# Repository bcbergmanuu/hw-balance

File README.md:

# Hardware deisgn balanceboard

Design Goals
  - Four measureable legs
  - USB 3 powered (<950mA)
  - Ultralow RMS Noise ldo (0.8µVRMS)
  - 10v Excitation voltage
  - Precision crystal clock fir filtering (20ppm)
  - Class c3 Loadcells type [LA250-D-100kg](https://allscaleseurope.com/content/uploads/2018/01/LA250-D-single-point-load-cell.pdf)
  - 8 bit decoupled auxiliary pc input
  - 24 bit ADC (ad7124)  

Balanceboard design

LTspice simulation LDO | Boost converters

Schematic Kicad | 3d-view of bcp

Errata:
R19 48K, should be 390
R3 should be removed

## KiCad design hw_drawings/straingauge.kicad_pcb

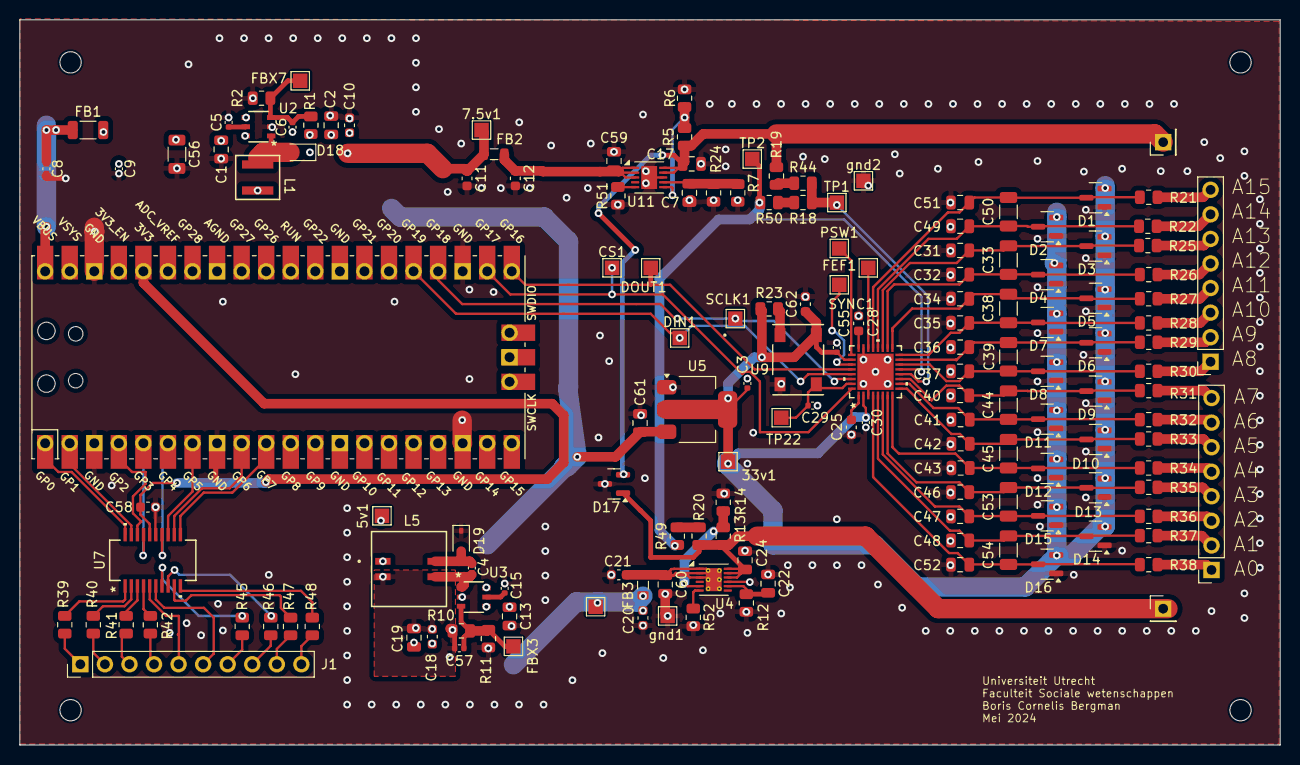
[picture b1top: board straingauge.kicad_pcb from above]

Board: 4 copper layers, 130.3 x 75.0 mm, 161 parts (0 on the bottom side), 98 nets.

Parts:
5v1, 7.5v1, 33v1: TestPoint_Pad_1.5x1.5mm
-3.8v1: TestPoint_Pad_1.5x1.5mm
C1, C2, C13, C17, C19, C24, C59, C60, C61: 10u; C_0805_2012Metric
C3, C4, C5, C8, C9, C15, C30, C55: 1u; C_0402_1005Metric
C6, C57: 4.7p; C_0402_1005Metric
C7, C22: 4.7u; C_0805_2012Metric
C10, C18, C25, C28, C58, C62: .1u; C_0603_1608Metric
C11, C12, C20, C21: 2.2u; C_0603_1608Metric
C29: 15p; C_0402_1005Metric
C31, C32, C34, C35, C36, C37, C40, C41, C42, C43, C46, C47, C48, C49, C51, C52: 10n; C_0805_2012Metric
C33, C38, C39, C44, C45, C50, C53, C54: 100n; C_1206_3216Metric
C56: 47u; R_1206_3216Metric
CS1: TestPoint_Pad_1.5x1.5mm
D1, D2, D3, D4, D5, D6, D7, D8, D9, D10, D11, D12, D13, D14, D15, D16: BAT54S; SOT-23
D17: BAV99; SOT-23
D18, D19: 1N5819WS; D_SOD-323
DIN1: TestPoint_Pad_1.5x1.5mm
DOUT1: TestPoint_Pad_1.5x1.5mm
FB1: 500 2A; L_1206_3216Metric
FB2, FB3: 120 1A; L_0805_2012Metric
FBX3, FBX7: TestPoint_Pad_1.5x1.5mm
FEF1: TestPoint_Pad_1.5x1.5mm
H1, H2, H3, H4: MountingHole_Pad; MountingHole_2.2mm_M2
J1: Conn_01x10_Pin; PinHeader_1x10_P2.54mm_Vertical
J2, J3: Conn_01x08_Pin; PinSocket_1x08_P2.54mm_Vertical
J4, J5: Pin; PinHeader_1x01_P2.54mm_Vertical
L1: XGL4020-152MEC; IND_XGL4020_COC
L5: 2.5u; IC4_MSD7342-252MLB_COC
PSW1: TestPoint_Pad_1.5x1.5mm
R1, R5, R10, R13: 1M; R_0805_2012Metric
R2, R11: 270K; R_0805_2012Metric
R6: 47K; R_0805_2012Metric
R7: 68k; R_0805_2012Metric
R12: 30k; R_0805_2012Metric
R14: 120K; R_0805_2012Metric
R18: 240; R_0805_2012Metric
R19: 430; R_0805_2012Metric
R20, R44, R50: 10; R_0805_2012Metric
R21, R22, R25, R26, R27, R28, R29, R30, R31, R32, R33, R34, R35, R36, R37, R38: 100; R_0805_2012Metric
R23: 1k; R_0805_2012Metric
R24: 2K; R_0805_2012Metric
R39, R40, R41, R42, R45, R46, R47, R48, R51: 680; R_0805_2012Metric
R49: 300; R_0805_2012Metric
R52: 16k; R_0805_2012Metric
SCLK1: TestPoint_Pad_1.5x1.5mm
SYNC1: TestPoint_Pad_1.5x1.5mm
TP1, TP2, TP22: TestPoint_Pad_1.5x1.5mm
U1: AD7124-8BCPZ; CP_32_12_ADI
U2, U3: LT8330ES6; TSOT-23_S6_LIT
U4: LT3094xDD; DFN-12-1EP_3x3mm_P0.45mm_EP1.65x2.38mm_ThermalVias
U5: AMS1117-3.3; SOT-223-3_TabPin2
U6: Pico; RPi_Pico_SMD_TH
U7: SI8380PM-IU; QSOP20_SIL
U9: SIT8008BC-83-33E-2.4576; SIT8008BC-83-33E-10.000000_SIT
U11: LT3045xDD; DFN-10-1EP_3x3mm_P0.5mm_EP1.65x2.38mm
gnd1, gnd2: TestPoint_Pad_1.5x1.5mm

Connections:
+3.3V: 33v1.1, C3.1, C30.1, C55.1, C62.1, D1.2 (K), D2.2 (K), D3.2 (K), D4.2 (K), D5.2 (K), D6.2 (K), D7.2 (K), D8.2 (K), D9.2 (K), D10.2 (K), D11.2 (K), D12.2 (K), D13.2 (K), D14.2 (K), D15.2 (K), D16.2 (K), R23.1, U1.2 (IOVDD), U1.26 (AVDD), U5.2 (VO), U9.4 (VDD)
+3.3VP: C58.1, U6.36 (3V3), U7.16 (VDD)
+5V: 5v1.1, C1.1, C9.1, C13.1, C56.1, C61.1, FB1.2, L1.2, L5.1, U2.4 (EN/UVLO), U2.6 (VIN), U3.4 (EN/UVLO), U3.6 (VIN), U5.3 (VI)
+5VP: C8.1, FB1.1, U6.40 (VBUS)
+7V: C17.1, D17.2 (A), J4.1, R5.1, R19.1, U11.9 (OUTS), U11.10 (OUT)
-3v: C24.1, D17.1 (K), J5.1, R13.2, R20.2, U4.10 (OUTS), U4.11 (OUT), U4.12 (OUT)
/7.526v: 7.5v1.1, C2.1, C6.1, C10.1, C11.1, D18.1 (K), FB2.1, R1.1
/*CS: CS1.1, U1.32 (*CS), U6.22 (GPIO17)
/-3.76v: -3.8v1.1, C18.2, C19.1, C20.1, C57.1, FB3.1, L5.2, R10.2
/AIN0: C52.2, C54.1, D16.3 (COM), R38.1, U1.4 (AIN0/IOUT/VBIAS)
/AIN0_C: J3.1, R38.2
/AIN1: C48.1, C54.2, D14.3 (COM), R37.1, U1.5 (AIN1/IOUT/VBIAS)
/AIN1_C: J3.2, R37.2
/AIN2: C47.2, C53.1, D15.3 (COM), R36.1, U1.6 (AIN2/IOUT/VBIAS/P1)
/AIN2_C: J3.3, R36.2
/AIN3: C46.1, C53.2, D13.3 (COM), R35.1, U1.7 (AIN3/IOUT/VBIAS/P2)
/AIN3_C: J3.4, R35.2
/AIN4: C43.2, C45.1, D12.3 (COM), R34.1, U1.8 (AIN4/IOUT/VBIAS/P3)
/AIN4_C: J3.5, R34.2
/AIN5: C42.1, C45.2, D10.3 (COM), R33.1, U1.9 (AIN5/IOUT/VBIAS/P4)
/AIN5_C: J3.6, R33.2
/AIN6: C41.2, C44.1, D11.3 (COM), R32.1, U1.10 (AIN6/IOUT/VBIAS)
/AIN6_C: J3.7, R32.2
/AIN7: C40.1, C44.2, D9.3 (COM), R31.1, U1.11 (AIN7/IOUT/VBIAS)
/AIN7_C: J3.8, R31.2
/AIN8: C37.2, C39.1, D8.3 (COM), R30.1, U1.14 (AIN8/IOUT/VBIAS)
/AIN8_C: J2.1, R30.2
/AIN9: C36.1, C39.2, D6.3 (COM), R29.1, U1.15 (AIN9/IOUT/VBIAS)
/AIN9_C: J2.2, R29.2
/AIN10: C35.2, C38.1, D7.3 (COM), R28.1, U1.16 (AIN10/IOUT/VBIAS)
/AIN10_C: J2.3, R28.2
/AIN11: C34.1, C38.2, D5.3 (COM), R27.1, U1.17 (AIN11/IOUT/VBIAS)
/AIN11_C: J2.4, R27.2
/AIN12: C32.2, C33.1, D4.3 (COM), R26.1, U1.18 (AIN12/IOUT/VBIAS)
/AIN12_C: J2.5, R26.2
/AIN13: C31.1, C33.2, D3.3 (COM), R25.1, U1.19 (AIN13/IOUT/VBIAS)
/AIN13_C: J2.6, R25.2
/AIN14: C49.2, C50.1, D2.3 (COM), R22.1, U1.20 (AIN14/IOUT/VBIAS/REFIN2(+))
/AIN14_C: J2.7, R22.2
/AIN15: C50.2, C51.1, D1.3 (COM), R21.1, U1.21 (AIN15/IOUT/VBIAS/REFIN2(-))
/AIN15_C: J2.8, R21.2
/CLK: C29.1, TP22.1, U1.31 (CLK), U9.3 (OUT)
/DIN: DIN1.1, U1.29 (DIN), U6.25 (GPIO19)
/DOUT/*RDY: DOUT1.1, U1.28 (DOUT/*RDY), U6.21 (GPIO16)
/REFIN1(+): R18.1, R44.2, TP1.1, U1.12 (REFIN1(+))
/REFIN1(-): R49.1, R50.2, TP2.1, U1.13 (REFIN1(-))
/SCLK: SCLK1.1, U1.30 (SCLK), U6.24 (GPIO18)
/in3: C21.1, C60.1, FB3.2, U4.1 (IN), U4.2 (IN), U4.3 (EN/UV), U4.13 (IN)
/in7: C12.1, C59.1, FB2.2, U11.1 (IN), U11.2 (IN), U11.3 (EN/UV)
/opto0: U6.1 (GPIO0), U7.20 (B1/BH1)
/opto1: U6.2 (GPIO1), U7.19 (B2/BH2)
/opto2: U6.4 (GPIO2), U7.18 (B3/BH3)
/opto3: U6.5 (GPIO3), U7.17 (B4/BH4)
/opto4: U6.6 (GPIO4), U7.14 (B5/BH5)
/opto5: U6.7 (GPIO5), U7.13 (B6/BH6)
/opto6: U6.9 (GPIO6), U7.12 (B7/BH7)
/opto7: U6.10 (GPIO7), U7.11 (B8/BH8)
GND: C1.2, C2.2, C3.2, C5.1, C7.2, C8.2, C9.2, C10.2, C11.2, C12.2, C13.2, C15.1, C17.2, C18.1, C19.2, C20.2, C21.2, C22.1, C24.2, C25.2, C28.2, C29.2, C30.2, C31.2, C32.1, C34.2, C35.1, C36.2, C37.1, C40.2, C41.1, C42.2, C43.1, C46.2, C47.1, C48.2, C49.1, C51.2, C52.1, C55.2, C56.2, C58.2, C59.2, C60.2, C61.2, C62.2, D1.1 (A), D2.1 (A), D3.1 (A), D4.1 (A), D5.1 (A), D6.1 (A), D7.1 (A), D8.1 (A), D9.1 (A), D10.1 (A), D11.1 (A), D12.1 (A), D13.1 (A), D14.1 (A), D15.1 (A), D16.1 (A), D17.3 (K), D19.1 (K), R2.2, R6.2, R7.2, R11.1, R12.1, R14.1, R24.2, R51.2, R52.2, U1.3 (DGND), U1.23 (AVSS), U1.33 (EP), U2.2 (GND), U3.2 (GND), U4.9 (GND), U5.1 (GND), U6.3 (GND), U6.8 (GND), U6.18 (GND), U6.23 (GND), U6.38 (GND), U7.15 (GND), U9.2 (GND), U11.8 (GND), U11.11 (GND), gnd1.1, gnd2.1
unnamed: D18.2 (A), L1.1, U2.1 (SW)
unnamed: C4.2, D19.2 (A), L5.4
unnamed: J1.1, R39.1
unnamed: J1.2, R40.1
unnamed: J1.3, R41.1
unnamed: J1.4, R42.1
unnamed: J1.5, U7.5 (COM)
unnamed: J1.6, U7.6 (COM)
unnamed: J1.7, R45.1
unnamed: J1.8, R46.1
unnamed: J1.9, R47.1
unnamed: J1.10, R48.1
unnamed: R18.2, R50.1
unnamed: R19.2, R44.1
unnamed: R20.1, R49.2
unnamed: SYNC1.1, U1.27 (*SYNC)
unnamed: PSW1.1, U1.25 (PSW)
unnamed: FEF1.1, U1.22 (REFOUT)
unnamed: C28.1, U1.24 (REGCAPA)
unnamed: C25.1, U1.1 (REGCAPD)
unnamed: C6.2, FBX7.1, R1.2, R2.1, U2.3 (FBX)
unnamed: C5.2, U2.5 (INTVCC)
unnamed: C57.2, FBX3.1, R10.1, R11.2, U3.3 (FBX)
unnamed: C15.2, U3.5 (INTVCC)
unnamed: C4.1, L5.3, U3.1 (SW)
unnamed: R52.1, U4.6 (ILIM)
unnamed: R13.1, R14.2, U4.5 (PGFB)
unnamed: C22.2, R12.2, U4.8 (SET)
unnamed: R39.2, U7.1 (A1/AH1)
unnamed: R40.2, U7.2 (A2/AH2)
unnamed: R41.2, U7.3 (A3/AH3)
unnamed: R42.2, U7.4 (A4/AH4)
unnamed: R45.2, U7.7 (A5/AH5)
unnamed: R46.2, U7.8 (A6/AH6)
unnamed: R47.2, U7.9 (A7/AH7)
unnamed: R48.2, U7.10 (A8/AH8)
unnamed: R23.2, U9.1 (OE/*ST/NC)
unnamed: R51.1, U11.5 (ILIM)
unnamed: R5.2, R6.1, U11.6 (PGFB)
unnamed: C7.1, R7.1, R24.1, U11.7 (SET)

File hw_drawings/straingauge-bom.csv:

"Id";"Designator";"Footprint";"Quantity";"Designation";"Supplier and ref";
1;"U9";"SIT8008BC-83-33E-10.000000_SIT";1;"SIT8008BC-83-33E-2.4576";;;
2;"U5,U2";"05-08-1699_ADI";2;"LT8333RDD-PBF";;;
3;"U1";"CP_32_12_ADI";1;"AD7124-8BCPZ";;;
4;"C23,C9,C5,C55,C8,C30,C15";"C_0402_1005Metric";7;"1u";;;
5;"FBX7,FBX3,gnd2,7.5v1,PSW1,gnd1,TP2,TP22,DIN1,DOUT1,FEF1,-3.8v1,TP1,5v1,33v1,SYNC1,CS1,SCLK1";"TestPoint_Pad_1.5x1.5mm";18;"~";;;
6;"C53,C33,C50,C39,C54,C38,C44,C45";"C_1206_3216Metric";8;"100n";;;
7;"R24";"R_0805_2012Metric";1;"2K";;;
8;"R6";"R_0805_2012Metric";1;"47K";;;
9;"C20,C11,C12,C21";"C_0603_1608Metric";4;"2.2u";;;
10;"R19";"R_0805_2012Metric";1;"430";;;
11;"C56";"R_1206_3216Metric";1;"47u";;;
12;"C43,C51,C34,C37,C31,C52,C40,C36,C49,C35,C48,C41,C47,C42,C32,C46";"C_0805_2012Metric";16;"10n";;;
13;"J1";"PinHeader_1x10_P2.54mm_Vertical";1;"Conn_01x10_Pin";;;
14;"C57,C6";"C_0402_1005Metric";2;"4.7p";;;
15;"CR2,CR3";"DIODE_DFN1608D-2_NEX";2;"PMEG4020EPK_315";;;
16;"R44,R50,R20";"R_0805_2012Metric";3;"10";;;
17;"R3,R7";"R_0805_2012Metric";2;"68k";;;
18;"R34,R28,R38,R25,R31,R32,R33,R36,R22,R27,R29,R37,R30,R21,R35,R26";"R_0805_2012Metric";16;"100";;;
19;"D8,D16,D7,D2,D14,D9,D1,D4,D15,D3,D10,D6,D13,D11,D12,D5";"SOT-23";16;"BAT54S";;;
20;"U4";"DFN-12-1EP_3x3mm_P0.45mm_EP1.65x2.38mm_ThermalVias";1;"LT3094xDD";;;
21;"R14";"R_0805_2012Metric";1;"120K";;;
22;"R41,R45,R42,R48,R47,R39,R40,R46";"R_0805_2012Metric";8;"680";;;
23;"R5,R16,R1,R10,R13";"R_0805_2012Metric";5;"1M";;;
24;"C4,C25,C62,C14,C58,C10,C18,C28";"C_0603_1608Metric";8;".1u";;;
25;"R43";"R_0805_2012Metric";1;"10k";;;
26;"C13,C60,C24,C59,C1,C2,C19,C27,C17,C61";"C_0805_2012Metric";10;"10u";;;
27;"L5";"IC4_MSD7342-252MLB_COC";1;"2.5u";;;
28;"U7";"QSOP20_SIL";1;"SI8380PM-IU";;;
29;"R2,R11";"R_0805_2012Metric";2;"270K";;;
30;"R4,R8";"R_0805_2012Metric";2;"20k";;;
31;"C26,C22,C7";"C_0805_2012Metric";3;"4.7u";;;
32;"J2,J3";"PinSocket_1x08_P2.54mm_Vertical";2;"Conn_01x08_Pin";;;
33;"L1";"IND_XGL4020_COC";1;"XGL4020-152MEC";;;
34;"L3,L4";"IND_NFZ18SM121SN10D_MUR";2;"NFZ18SM121SN10D";;;
35;"R23";"R_0805_2012Metric";1;"1k";;;
36;"U6";"RPi_Pico_SMD_TH";1;"Pico";;;
37;"R15";"R_0805_2012Metric";1;"33k";;;
38;"J4,J5";"PinHeader_1x01_P2.54mm_Vertical";2;"Pin";;;
39;"R18";"R_0805_2012Metric";1;"240";;;
40;"R49";"R_0805_2012Metric";1;"300";;;
41;"R17";"R_0805_2012Metric";1;"100k";;;
42;"R9";"R_0805_2012Metric";1;"39k";;;
43;"C29";"C_0402_1005Metric";1;"15p";;;
44;"C3";"C_0603_1608Metric";1;"680p";;;
45;"L2";"IND_742792040_WRE";1;"742792040";;;
46;"U11,U10";"DFN-10-1EP_3x3mm_P0.5mm_EP1.65x2.38mm";2;"LT3045xDD";;;
47;"R12";"R_0805_2012Metric";1;"30k";;;
48;"C16";"C_0603_1608Metric";1;"1.5n";;;

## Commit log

2024-04-22 images
2024-04-29 drawing schematic
2024-04-30 finished schematic
2024-05-01 pcb1
2024-05-02 fixed ERC
2024-05-02 supplies
2024-05-03 full pcb
2024-05-03 full pcb1
2024-05-05 finished project
2024-05-05 changed bead
2024-05-06 move l5
2024-05-12 redesign
2024-05-12 new schematic
